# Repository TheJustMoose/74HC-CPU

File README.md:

# 74HCPU

Not a very scary instruction set discrete logic processor.

* 8 bit data
* 16 bit address / 64KB RAM
* 16 instructions
* 8 data registers and 4 pointer registers in 2 banks
* 1 flag register in IO port

## How CPU works?

[Layers of PCBs](layers/README.md)

## Instruction list

```
|----------------------------------------------|f|
|   HIGH BYTE    |    LOW BYTE   |  HIGH BYTE  |a|
|0 1 2 3  4 5 6 7 8 9 A B C D E F|   (again)   |g|
|   4   +   3 + 1 + 3  +    5    = 16          |l|
|----------------------------------------------|s|
|   ADD |  DST |C| SRC |-|Z|z|I|i| 00 0000 0000|*|
|  ADDC |  DST |C| SRC |F|Z|z|I|i| 10 0001 0000|*|
|   AND |  DST |C| SRC |-|Z|z|I|i| 20 0010 0000|*|
|    OR |  DST |C| SRC |-|Z|z|I|i| 30 0011 0000|*|
|   XOR |  DST |C| SRC |-|Z|z|I|i| 40 0100 0000|*|
|   MUL |  DST |C| SRC |-|Z|z|I|i| 50 0101 0000|*|
|   UNO |  DST |0|-|TYP|F|-|-|-|-| 60 0110 0000|*|
|   MOV |  DST |0| SRC |*|Z|z|I|i| 70 0111 0000| |
|   LPM |  DST |W|EXT|D|U|OFFSET4| 80 1000 0000| |
|    LD |  DST |0|EXT|D|U|OFFSET4| 90 1001 0000| |
|    IN |  DST |  PORT   |Z|z|I|i| A0 1010 0000| |
|--------------|7-8-9-A-B|-------|-------------|-|
|   OUT |  SRC |  PORT   |O|o|X|x| B0 1011 0000| |
|    ST |  SRC |0|EXT|D|U|OFFSET4| C0 1100 0000| |
|   CMP |  DST |C| SRC |-|   -   | D0 1101 0000|+|
|  CMPC |  DST |C| SRC |-|   -   | E0 1110 0000|+|
| BRNCH |  CALL  | 8 bit OFFSET  | F0 1111 0000| |
| BRNCH |   JMP  | 8 bit OFFSET  | F1 1111 0001| |
| BRNCH |   RET  | 8 bit +STACK  | F2 1111 0010| |
| BRNCH |  RETI  | 8 bit OFFSET  | F3 1111 0011| |
| BRNCH |    JL  | 8 bit OFFSET  | F4 1111 0100| |
| BRNCH |    JE  | 8 bit OFFSET  | F5 1111 0101| |
| BRNCH |   JNE  | 8 bit OFFSET  | F6 1111 0110| |
| BRNCH |    JG  | 8 bit OFFSET  | F7 1111 0111| |
| BRNCH |    JZ  | 8 bit OFFSET  | F8 1111 1000| |
| BRNCH |   JNZ  | 8 bit OFFSET  | F9 1111 1001| |
| BRNCH |    JC  | 8 bit OFFSET  | FA 1111 1010| |
| BRNCH |   JNC  | 8 bit OFFSET  | FB 1111 1011| |
| BRNCH |   JHC  | 8 bit OFFSET  | FC 1111 1100| |
| BRNCH |  JNHC  | 8 bit OFFSET  | FD 1111 1101| |
| BRNCH | AFCALL | Hi 8 bit ADDR | FE 1111 1110| |
| BRNCH |NOP/STOP|   1111 111x   | FF 1111 1111| |
|----------------------------------------------|-|
```

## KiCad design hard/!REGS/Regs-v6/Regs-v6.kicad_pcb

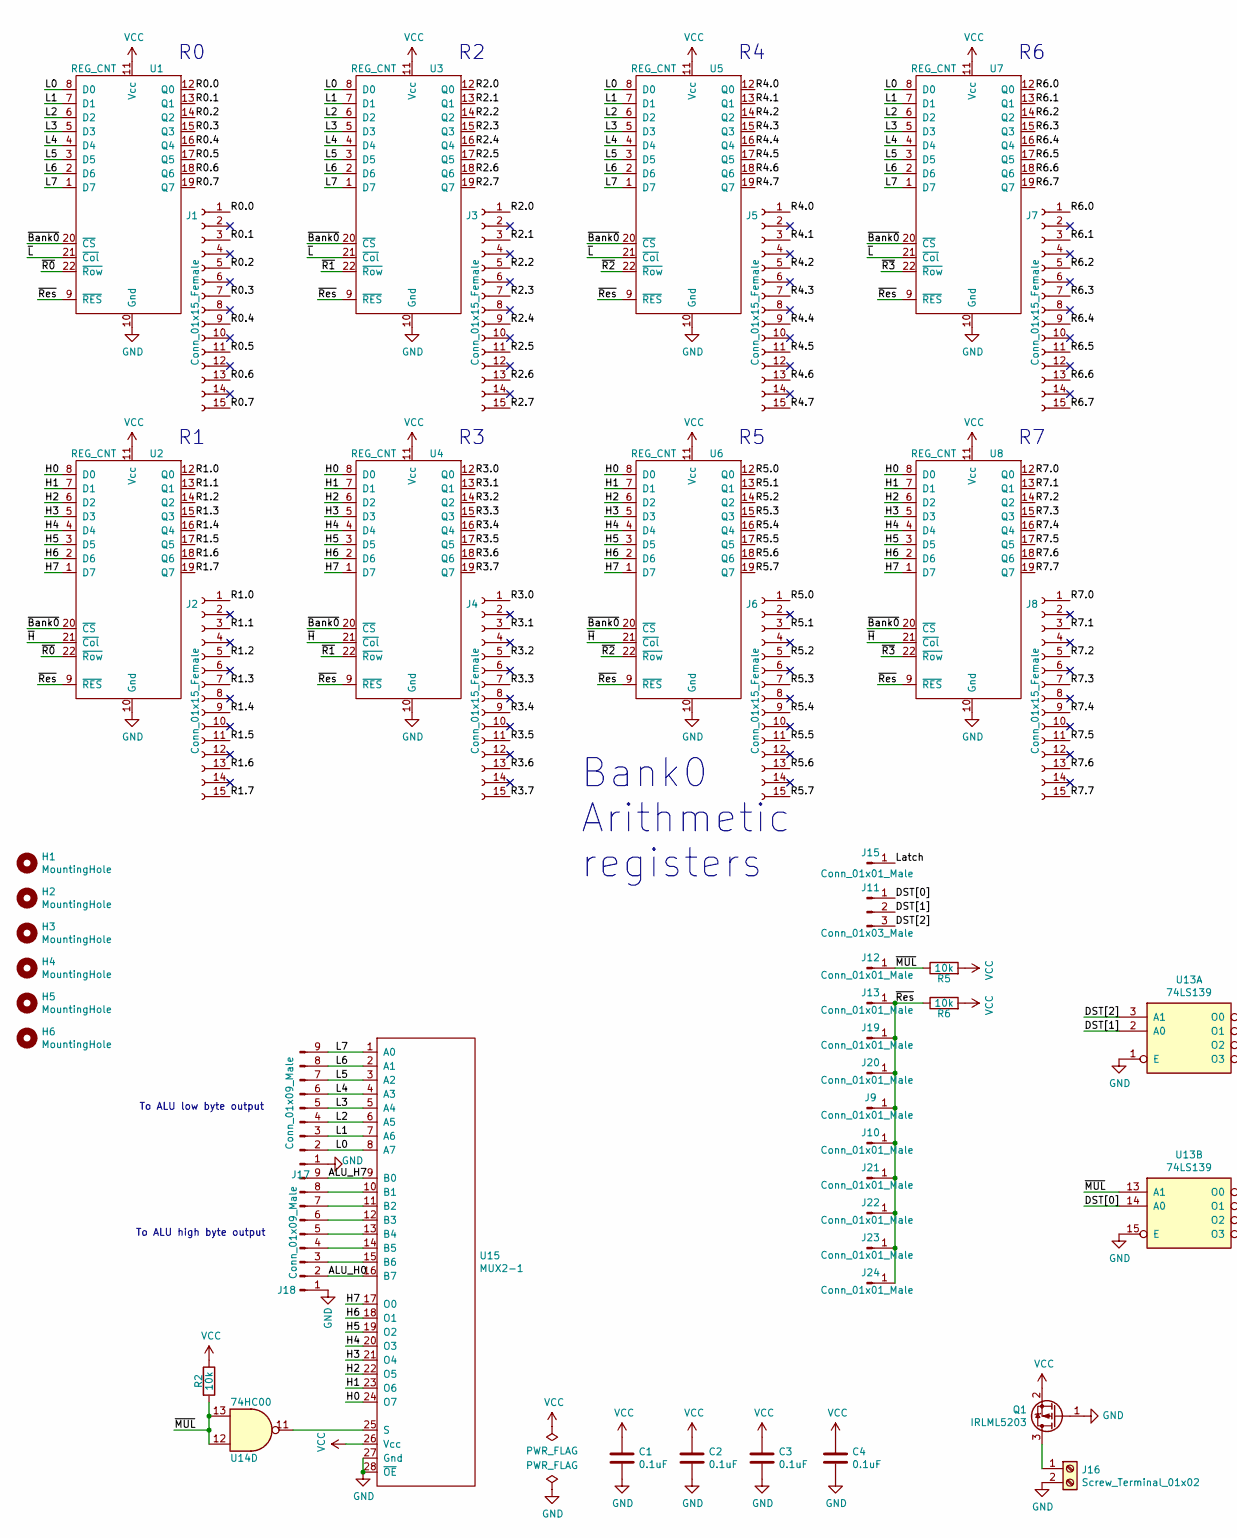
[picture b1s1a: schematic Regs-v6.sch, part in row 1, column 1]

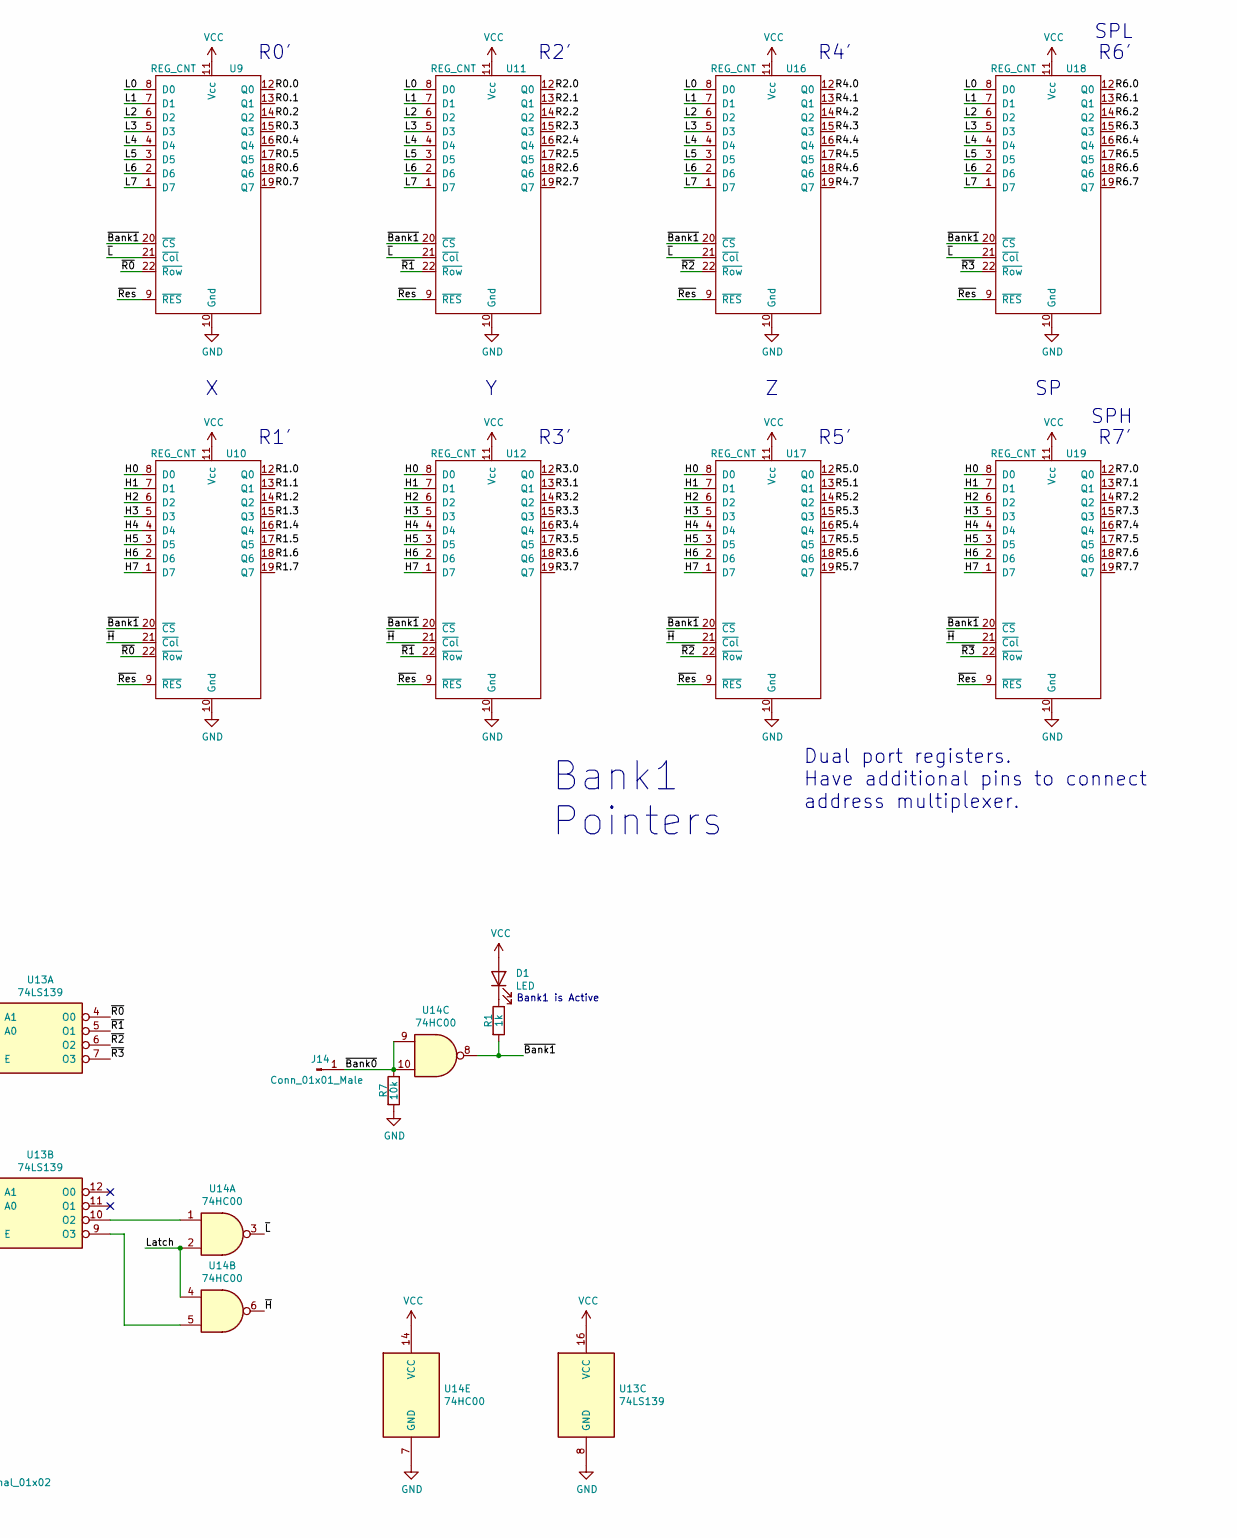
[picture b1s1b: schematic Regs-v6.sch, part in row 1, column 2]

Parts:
C1, C2, C3, C4: 0.1uF; C_0805_2012Metric_Pad1.18x1.45mm_HandSolder
D1: LED; LED_D5.0mm
H1, H2, H3, H4, H5, H6: MountingHole; MountingHole_3.2mm_M3
J1, J2, J3, J4, J5, J6, J7, J8: Conn_01x15_Female; PinSocket_1x15_P2.54mm_Vertical
J9, J10, J12, J13, J14, J15, J19, J20, J21, J22, J23, J24: Conn_01x01_Male; PinHeader_1x01_P2.54mm_Vertical
J11: Conn_01x03_Male; PinHeader_1x03_P2.54mm_Vertical
J16: Screw_Terminal_01x02; TerminalBlock_Phoenix_MKDS-1,5-2_1x02_P5.00mm_Horizontal
J17, J18: Conn_01x09_Male; PinHeader_1x09_P2.54mm_Vertical
Q1: IRLML5203; SOT-23
R1: 1k; R_0805_2012Metric_Pad1.20x1.40mm_HandSolder
R2, R5, R6, R7: 10k; R_0805_2012Metric_Pad1.20x1.40mm_HandSolder
U1, U2, U3, U4, U5, U6, U7, U8, U9, U10, U11, U12, U16, U17, U18, U19: REG_CNT
U13: 74LS139; DIP-16_W7.62mm_Socket
U14: 74HC00; DIP-14_W7.62mm_Socket
U15: MUX2-1; CMDwoC

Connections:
/ALU_H0: J18.2, U15.16 (B7)
/ALU_H7: J18.9, U15.9 (B0)
/DST[0]: J11.1, U13.14 (A0)
/DST[1]: J11.2, U13.2 (A0)
/DST[2]: J11.3, U13.3 (A1)
/H0: U2.8 (D0), U4.8 (D0), U6.8 (D0), U8.8 (D0), U10.8 (D0), U12.8 (D0), U15.24 (O7), U17.8 (D0), U19.8 (D0)
/H1: U2.7 (D1), U4.7 (D1), U6.7 (D1), U8.7 (D1), U10.7 (D1), U12.7 (D1), U15.23 (O6), U17.7 (D1), U19.7 (D1)
/H2: U2.6 (D2), U4.6 (D2), U6.6 (D2), U8.6 (D2), U10.6 (D2), U12.6 (D2), U15.22 (O5), U17.6 (D2), U19.6 (D2)
/H3: U2.5 (D3), U4.5 (D3), U6.5 (D3), U8.5 (D3), U10.5 (D3), U12.5 (D3), U15.21 (O4), U17.5 (D3), U19.5 (D3)
/H4: U2.4 (D4), U4.4 (D4), U6.4 (D4), U8.4 (D4), U10.4 (D4), U12.4 (D4), U15.20 (O3), U17.4 (D4), U19.4 (D4)
/H5: U2.3 (D5), U4.3 (D5), U6.3 (D5), U8.3 (D5), U10.3 (D5), U12.3 (D5), U15.19 (O2), U17.3 (D5), U19.3 (D5)
/H6: U2.2 (D6), U4.2 (D6), U6.2 (D6), U8.2 (D6), U10.2 (D6), U12.2 (D6), U15.18 (O1), U17.2 (D6), U19.2 (D6)
/H7: U2.1 (D7), U4.1 (D7), U6.1 (D7), U8.1 (D7), U10.1 (D7), U12.1 (D7), U15.17 (O0), U17.1 (D7), U19.1 (D7)
/L0: J17.2, U1.8 (D0), U3.8 (D0), U5.8 (D0), U7.8 (D0), U9.8 (D0), U11.8 (D0), U15.8 (A7), U16.8 (D0), U18.8 (D0)
/L1: J17.3, U1.7 (D1), U3.7 (D1), U5.7 (D1), U7.7 (D1), U9.7 (D1), U11.7 (D1), U15.7 (A6), U16.7 (D1), U18.7 (D1)
/L2: J17.4, U1.6 (D2), U3.6 (D2), U5.6 (D2), U7.6 (D2), U9.6 (D2), U11.6 (D2), U15.6 (A5), U16.6 (D2), U18.6 (D2)
/L3: J17.5, U1.5 (D3), U3.5 (D3), U5.5 (D3), U7.5 (D3), U9.5 (D3), U11.5 (D3), U15.5 (A4), U16.5 (D3), U18.5 (D3)
/L4: J17.6, U1.4 (D4), U3.4 (D4), U5.4 (D4), U7.4 (D4), U9.4 (D4), U11.4 (D4), U15.4 (A3), U16.4 (D4), U18.4 (D4)
/L5: J17.7, U1.3 (D5), U3.3 (D5), U5.3 (D5), U7.3 (D5), U9.3 (D5), U11.3 (D5), U15.3 (A2), U16.3 (D5), U18.3 (D5)
/L6: J17.8, U1.2 (D6), U3.2 (D6), U5.2 (D6), U7.2 (D6), U9.2 (D6), U11.2 (D6), U15.2 (A1), U16.2 (D6), U18.2 (D6)
/L7: J17.9, U1.1 (D7), U3.1 (D7), U5.1 (D7), U7.1 (D7), U9.1 (D7), U11.1 (D7), U15.1 (A0), U16.1 (D7), U18.1 (D7)
/Latch: J15.1, U14.2, U14.4
/R0.0: J1.1, U1.12 (Q0), U9.12 (Q0)
/R0.1: J1.3, U1.13 (Q1), U9.13 (Q1)
/R0.2: J1.5, U1.14 (Q2), U9.14 (Q2)
/R0.3: J1.7, U1.15 (Q3), U9.15 (Q3)
/R0.4: J1.9, U1.16 (Q4), U9.16 (Q4)
/R0.5: J1.11, U1.17 (Q5), U9.17 (Q5)
/R0.6: J1.13, U1.18 (Q6), U9.18 (Q6)
/R0.7: J1.15, U1.19 (Q7), U9.19 (Q7)
/R1.0: J2.1, U2.12 (Q0), U10.12 (Q0)
/R1.1: J2.3, U2.13 (Q1), U10.13 (Q1)
/R1.2: J2.5, U2.14 (Q2), U10.14 (Q2)
/R1.3: J2.7, U2.15 (Q3), U10.15 (Q3)
/R1.4: J2.9, U2.16 (Q4), U10.16 (Q4)
/R1.5: J2.11, U2.17 (Q5), U10.17 (Q5)
/R1.6: J2.13, U2.18 (Q6), U10.18 (Q6)
/R1.7: J2.15, U2.19 (Q7), U10.19 (Q7)
/R2.0: J3.1, U3.12 (Q0), U11.12 (Q0)
/R2.1: J3.3, U3.13 (Q1), U11.13 (Q1)
/R2.2: J3.5, U3.14 (Q2), U11.14 (Q2)
/R2.3: J3.7, U3.15 (Q3), U11.15 (Q3)
/R2.4: J3.9, U3.16 (Q4), U11.16 (Q4)
/R2.5: J3.11, U3.17 (Q5), U11.17 (Q5)
/R2.6: J3.13, U3.18 (Q6), U11.18 (Q6)
/R2.7: J3.15, U3.19 (Q7), U11.19 (Q7)
/R3.0: J4.1, U4.12 (Q0), U12.12 (Q0)
/R3.1: J4.3, U4.13 (Q1), U12.13 (Q1)
/R3.2: J4.5, U4.14 (Q2), U12.14 (Q2)
/R3.3: J4.7, U4.15 (Q3), U12.15 (Q3)
/R3.4: J4.9, U4.16 (Q4), U12.16 (Q4)
/R3.5: J4.11, U4.17 (Q5), U12.17 (Q5)
/R3.6: J4.13, U4.18 (Q6), U12.18 (Q6)
/R3.7: J4.15, U4.19 (Q7), U12.19 (Q7)
/R4.0: J5.1, U5.12 (Q0), U16.12 (Q0)
/R4.1: J5.3, U5.13 (Q1), U16.13 (Q1)
/R4.2: J5.5, U5.14 (Q2), U16.14 (Q2)
/R4.3: J5.7, U5.15 (Q3), U16.15 (Q3)
/R4.4: J5.9, U5.16 (Q4), U16.16 (Q4)
/R4.5: J5.11, U5.17 (Q5), U16.17 (Q5)
/R4.6: J5.13, U5.18 (Q6), U16.18 (Q6)
/R4.7: J5.15, U5.19 (Q7), U16.19 (Q7)
/R5.0: J6.1, U6.12 (Q0), U17.12 (Q0)
/R5.1: J6.3, U6.13 (Q1), U17.13 (Q1)
/R5.2: J6.5, U6.14 (Q2), U17.14 (Q2)
/R5.3: J6.7, U6.15 (Q3), U17.15 (Q3)
/R5.4: J6.9, U6.16 (Q4), U17.16 (Q4)
/R5.5: J6.11, U6.17 (Q5), U17.17 (Q5)
/R5.6: J6.13, U6.18 (Q6), U17.18 (Q6)
/R5.7: J6.15, U6.19 (Q7), U17.19 (Q7)
/R6.0: J7.1, U7.12 (Q0), U18.12 (Q0)
/R6.1: J7.3, U7.13 (Q1), U18.13 (Q1)
/R6.2: J7.5, U7.14 (Q2), U18.14 (Q2)
/R6.3: J7.7, U7.15 (Q3), U18.15 (Q3)
/R6.4: J7.9, U7.16 (Q4), U18.16 (Q4)
/R6.5: J7.11, U7.17 (Q5), U18.17 (Q5)
/R6.6: J7.13, U7.18 (Q6), U18.18 (Q6)
/R6.7: J7.15, U7.19 (Q7), U18.19 (Q7)
/R7.0: J8.1, U8.12 (Q0), U19.12 (Q0)
/R7.1: J8.3, U8.13 (Q1), U19.13 (Q1)
/R7.2: J8.5, U8.14 (Q2), U19.14 (Q2)
/R7.3: J8.7, U8.15 (Q3), U19.15 (Q3)
/R7.4: J8.9, U8.16 (Q4), U19.16 (Q4)
/R7.5: J8.11, U8.17 (Q5), U19.17 (Q5)
/R7.6: J8.13, U8.18 (Q6), U19.18 (Q6)
/R7.7: J8.15, U8.19 (Q7), U19.19 (Q7)
/~Bank0: J14.1, R7.1, U1.20 (~CS), U2.20 (~CS), U3.20 (~CS), U4.20 (~CS), U5.20 (~CS), U6.20 (~CS), U7.20 (~CS), U8.20 (~CS), U14.9, U14.10
/~Bank1: R1.2, U9.20 (~CS), U10.20 (~CS), U11.20 (~CS), U12.20 (~CS), U14.8, U16.20 (~CS), U17.20 (~CS), U18.20 (~CS), U19.20 (~CS)
/~H: U2.21 (~Col), U4.21 (~Col), U6.21 (~Col), U8.21 (~Col), U10.21 (~Col), U12.21 (~Col), U14.6, U17.21 (~Col), U19.21 (~Col)
/~L: U1.21 (~Col), U3.21 (~Col), U5.21 (~Col), U7.21 (~Col), U9.21 (~Col), U11.21 (~Col), U14.3, U16.21 (~Col), U18.21 (~Col)
/~MUL: J12.1, R2.2, R5.1, U13.13 (A1), U14.12, U14.13
/~R0: U1.22 (~Row), U2.22 (~Row), U9.22 (~Row), U10.22 (~Row), U13.4 (O0)
/~R1: U3.22 (~Row), U4.22 (~Row), U11.22 (~Row), U12.22 (~Row), U13.5 (O1)
/~R2: U5.22 (~Row), U6.22 (~Row), U13.6 (O2), U16.22 (~Row), U17.22 (~Row)
/~R3: U7.22 (~Row), U8.22 (~Row), U13.7 (O3), U18.22 (~Row), U19.22 (~Row)
/~Res: J9.1, J10.1, J13.1, J19.1, J20.1, J21.1, J22.1, J23.1, J24.1, R6.1, U1.9 (~RES), U2.9 (~RES), U3.9 (~RES), U4.9 (~RES), U5.9 (~RES), U6.9 (~RES), U7.9 (~RES), U8.9 (~RES), U9.9 (~RES), U10.9 (~RES), U11.9 (~RES), U12.9 (~RES), U16.9 (~RES), U17.9 (~RES), U18.9 (~RES), U19.9 (~RES)
GND: C1.2, C2.2, C3.2, C4.2, J16.2, J17.1, J18.1, Q1.1 (G), R7.2, U1.10 (Gnd), U2.10 (Gnd), U3.10 (Gnd), U4.10 (Gnd), U5.10 (Gnd), U6.10 (Gnd), U7.10 (Gnd), U8.10 (Gnd), U9.10 (Gnd), U10.10 (Gnd), U11.10 (Gnd), U12.10 (Gnd), U13.1 (E), U13.8 (GND), U13.15 (E), U14.7 (GND), U15.27 (Gnd), U15.28 (~OE), U16.10 (Gnd), U17.10 (Gnd), U18.10 (Gnd), U19.10 (Gnd)
unnamed: D1.1 (K), R1.1
unnamed: J16.1, Q1.3 (D)
unnamed: J18.3, U15.15 (B6)
unnamed: J18.4, U15.14 (B5)
unnamed: J18.5, U15.13 (B4)
unnamed: J18.6, U15.12 (B3)
unnamed: J18.7, U15.11 (B2)
unnamed: J18.8, U15.10 (B1)
unnamed: U13.9 (O3), U14.5
unnamed: U13.10 (O2), U14.1
unnamed: U14.11, U15.25 (S)
VCC: C1.1, C2.1, C3.1, C4.1, D1.2 (A), Q1.2 (S), R2.1, R5.2, R6.2, U1.11 (Vcc), U2.11 (Vcc), U3.11 (Vcc), U4.11 (Vcc), U5.11 (Vcc), U6.11 (Vcc), U7.11 (Vcc), U8.11 (Vcc), U9.11 (Vcc), U10.11 (Vcc), U11.11 (Vcc), U12.11 (Vcc), U13.16 (VCC), U14.14 (VCC), U15.26 (Vcc), U16.11 (Vcc), U17.11 (Vcc), U18.11 (Vcc), U19.11 (Vcc)

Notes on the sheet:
SPL
SPH
To ALU low byte output
To ALU high byte output
R0'
R4'
R2'
R6'
R7'
R5'
R3'
R1'
Bank0 Arithmetic registers
Bank1 Pointers
Dual port registers. Have additional pins to connect address multiplexer.
Bank1 is Active

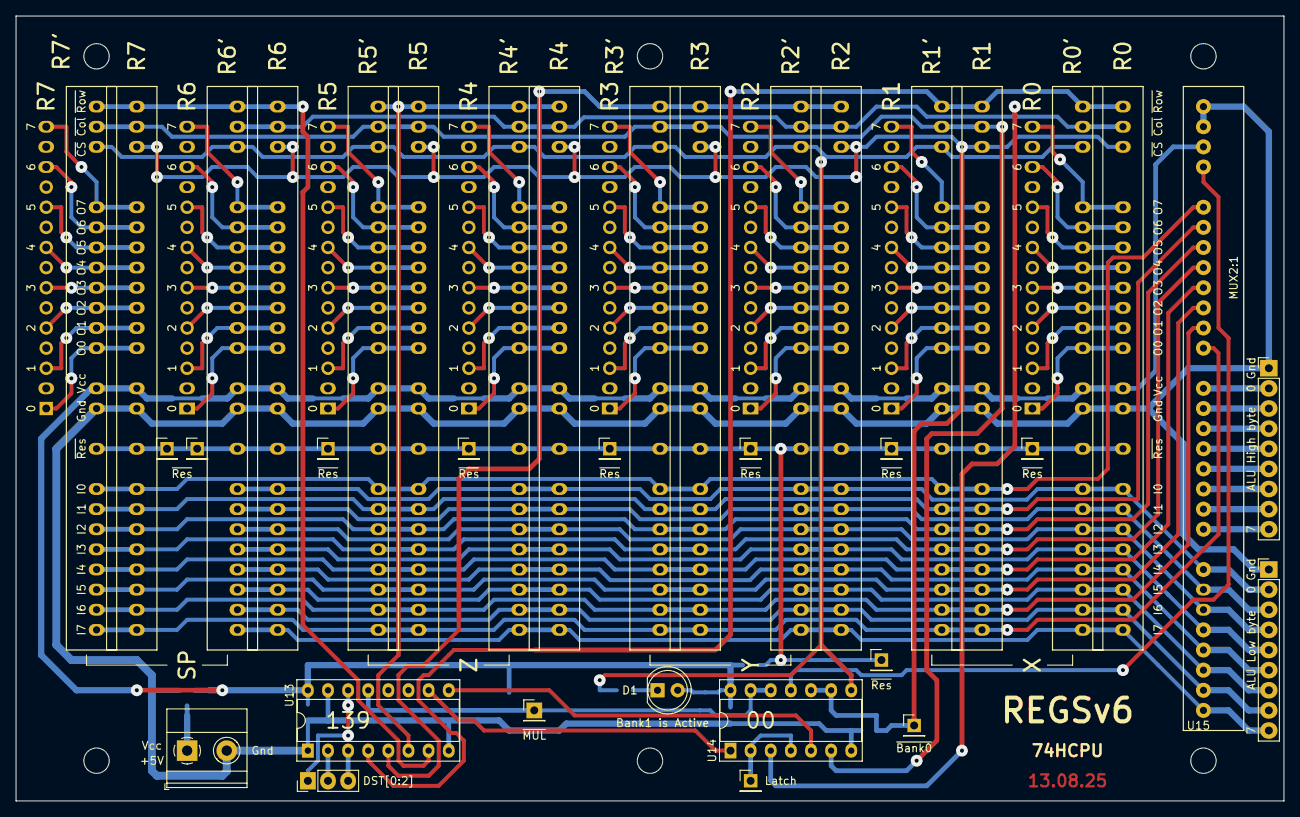
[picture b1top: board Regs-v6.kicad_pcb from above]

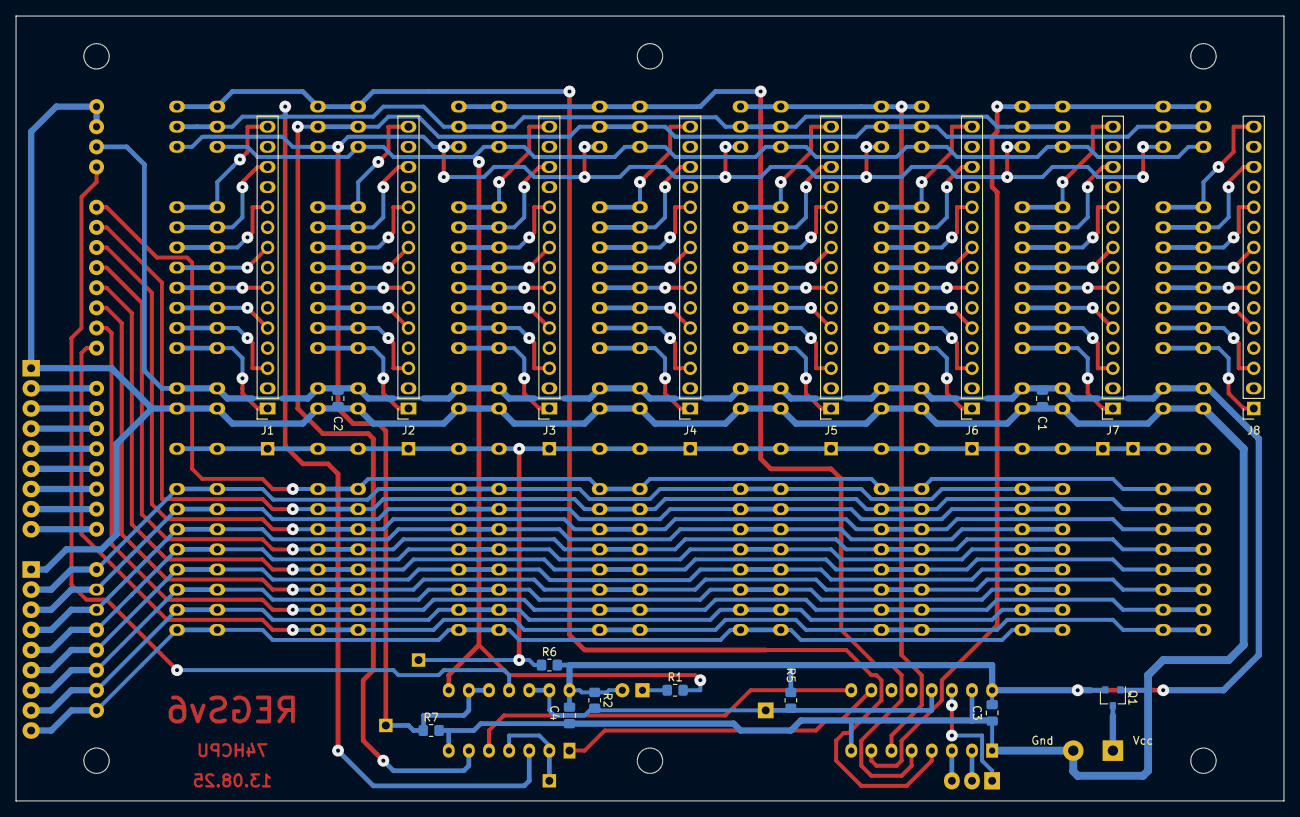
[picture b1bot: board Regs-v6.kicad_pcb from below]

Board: 2 copper layers, 160.0 x 99.1 mm, 60 parts (18 on the bottom side), 109 nets.

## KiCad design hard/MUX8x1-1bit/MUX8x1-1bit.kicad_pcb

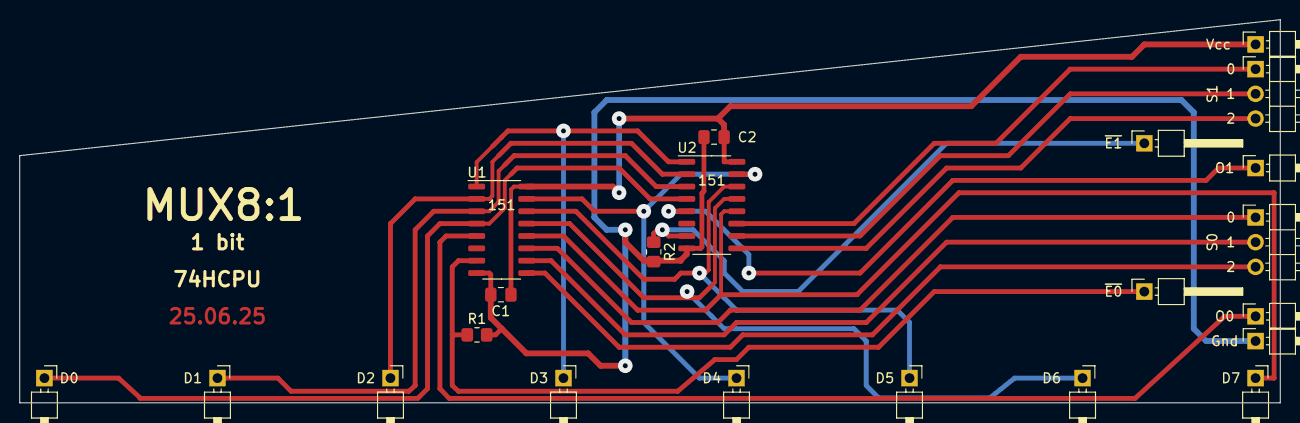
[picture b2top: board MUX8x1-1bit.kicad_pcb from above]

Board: 2 copper layers, 129.5 x 39.4 mm, 22 parts (0 on the bottom side), 20 nets.

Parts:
C1, C2: 0.1uF; C_0805_2012Metric_Pad1.18x1.45mm_HandSolder
J1, J2, J3, J4, J5, J6, J7, J8, J10, J11, J13, J14, J15, J16: Conn_01x01_Male; PinHeader_1x01_P2.54mm_Horizontal
J9, J12: Conn_01x03_Male; PinHeader_1x03_P2.54mm_Horizontal
R1, R2: 10k; R_0805_2012Metric_Pad1.20x1.40mm_HandSolder
U1, U2: 74LS151; SO-16_3.9x9.9mm_P1.27mm

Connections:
/D0: J1.1, U1.4, U2.4
/D1: J2.1, U1.3, U2.3
/D2: J3.1, U1.2, U2.2
/D3: J4.1, U1.1, U2.1
/D4: J5.1, U1.15, U2.15
/D5: J6.1, U1.14, U2.14
/D6: J7.1, U1.13, U2.13
/D7: J8.1, U1.12, U2.12
/O0: J11.1, U1.5
/O1: J14.1, U2.5
/S0.0: J9.1, U1.11
/S0.1: J9.2, U1.10
/S0.2: J9.3, U1.9
/S1.0: J12.1, U2.11
/S1.1: J12.2, U2.10
/S1.2: J12.3, U2.9
/~E0: J10.1, R1.1, U1.7
/~E1: J13.1, R2.1, U2.7
GND: C1.2, C2.2, J16.1, R1.2, R2.2, U1.8, U2.8
VCC: C1.1, C2.1, J15.1, U1.16, U2.16

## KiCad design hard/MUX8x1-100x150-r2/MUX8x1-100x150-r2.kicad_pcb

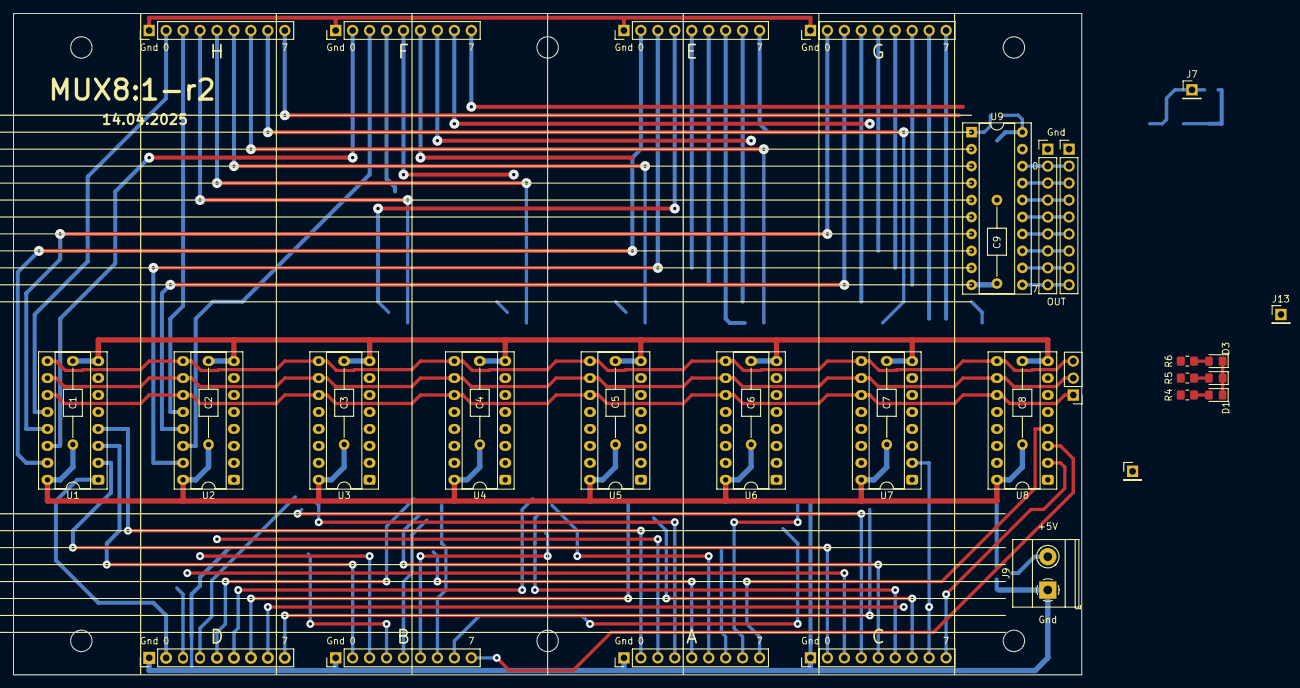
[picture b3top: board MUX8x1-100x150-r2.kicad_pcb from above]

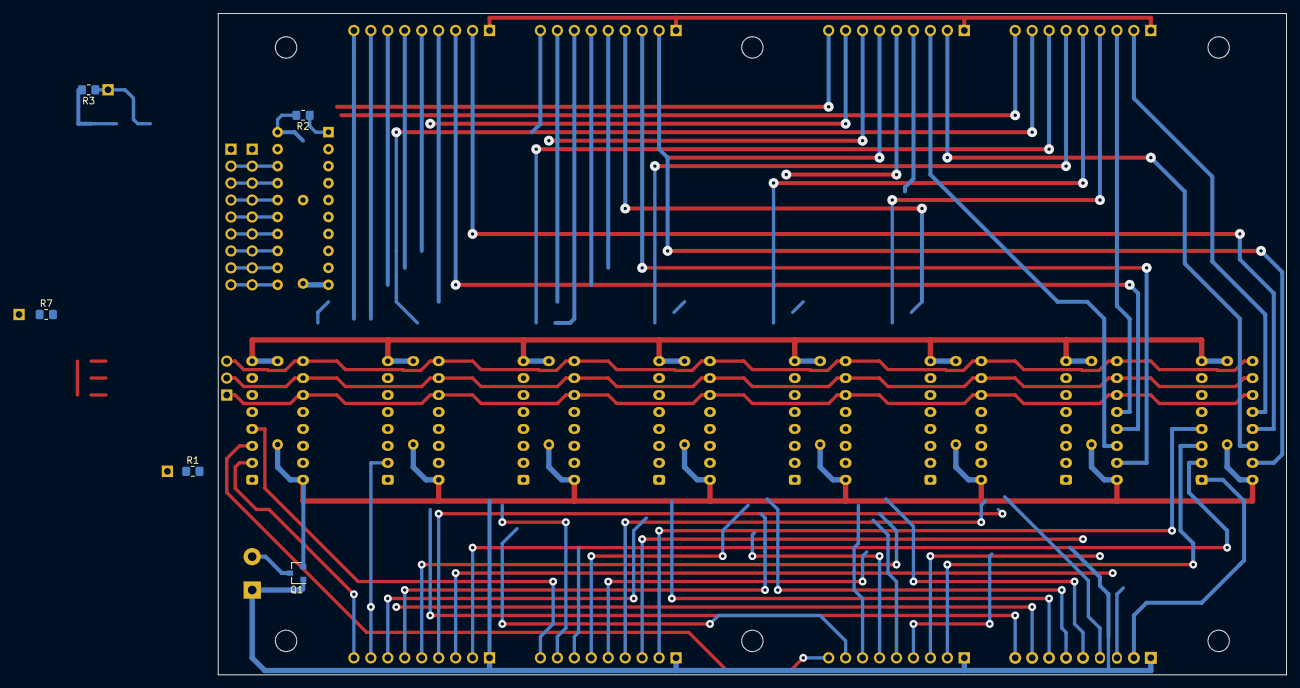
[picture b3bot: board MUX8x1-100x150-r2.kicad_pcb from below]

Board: 2 copper layers, 160.0 x 99.1 mm, 50 parts (5 on the bottom side), 93 nets.

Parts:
C1, C2, C3, C4, C5, C6, C7, C8, C9: 0.1uF; C_Axial_L3.8mm_D2.6mm_P12.50mm_Horizontal
D1, D2, D3: LED; LED_0805_2012Metric_Pad1.15x1.40mm_HandSolder
H1, H2, H3, H4, H5, H6: MountingHole; MountingHole_3.2mm_M3
J1, J2, J3, J5, J6, J11, J12, J15, J16, J21: Conn_01x09_Male; PinHeader_1x09_P2.54mm_Vertical
J7, J13, J20: Conn_01x01_Male; PinHeader_1x01_P2.54mm_Vertical
J9: Screw_Terminal_01x02; TerminalBlock_Phoenix_MKDS-1,5-2_1x02_P5.00mm_Horizontal
J10: Conn_01x03_Male; PinHeader_1x03_P2.54mm_Vertical
Q1: IRLML5203; SOT-23
R1, R2, R3, R7: 10k; R_0805_2012Metric_Pad1.20x1.40mm_HandSolder
R4, R5, R6: 1k; R_0805_2012Metric_Pad1.20x1.40mm_HandSolder
U1, U2, U3, U4, U5, U6, U7, U8: 74LS151; DIP-16_W7.62mm_Socket
U9: 74HC245; DIP-20_W7.62mm_Socket

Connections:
/A0: J1.2, U1.4
/A1: J1.3, U2.4
/A2: J1.4, U3.4
/A3: J1.5, U4.4
/A4: J1.6, U5.4
/A5: J1.7, U6.4
/A6: J1.8, U7.4
/A7: J1.9, U8.4
/B0: J5.2, U1.3
/B1: J5.3, U2.3
/B2: J5.4, U3.3
/B3: J5.5, U4.3
/B4: J5.6, U5.3
/B5: J5.7, U6.3
/B6: J5.8, U7.3
/B7: J5.9, U8.3
/BUS0: J3.2, J21.2, U9.18
/BUS1: J3.3, J21.3, U9.17
/BUS2: J3.4, J21.4, U9.16
/BUS3: J3.5, J21.5, U9.15
/BUS4: J3.6, J21.6, U9.14
/BUS5: J3.7, J21.7, U9.13
/BUS6: J3.8, J21.8, U9.12
/BUS7: J3.9, J21.9, U9.11
/C0: J11.2, U1.2
/C1: J11.3, U2.2
/C2: J11.4, U3.2
/C3: J11.5, U4.2
/C4: J11.6, U5.2
/C5: J11.7, U6.2
/C6: J11.8, U7.2
/C7: J11.9, U8.2
/D0: J15.2, U1.1
/D1: J15.3, U2.1
/D2: J15.4, U3.1
/D3: J15.5, U4.1
/D4: J15.6, U5.1
/D5: J15.7, U6.1
/D6: J15.8, U7.1
/D7: J15.9, U8.1
/E0: J2.2, U1.15
/E1: J2.3, U2.15
/E2: J2.4, U3.15
/E3: J2.5, U4.15
/E4: J2.6, U5.15
/E5: J2.7, U6.15
/E6: J2.8, U7.15
/E7: J2.9, U8.15
/F0: J6.2, U1.14
/F1: J6.3, U2.14
/F2: J6.4, U3.14
/F3: J6.5, U4.14
/F4: J6.6, U5.14
/F5: J6.7, U6.14
/F6: J6.8, U7.14
/F7: J6.9, U8.14
/G0: J12.2, U1.13
/G1: J12.3, U2.13
/G2: J12.4, U3.13
/G3: J12.5, U4.13
/G4: J12.6, U5.13
/G5: J12.7, U6.13
/G6: J12.8, U7.13
/G7: J12.9, U8.13
/H0: J16.2, U1.12
/H1: J16.3, U2.12
/H2: J16.4, U3.12
/H3: J16.5, U4.12
/H4: J16.6, U5.12
/H5: J16.7, U6.12
/H6: J16.8, U7.12
/H7: J16.9, U8.12
/O0: U1.5, U9.2
/O1: U2.5, U9.3
/O2: U3.5, U9.4
/O3: U4.5, U9.5
/O4: U5.5, U9.6
/O5: U6.5, U9.7
/O6: U7.5, U9.8
/O7: U8.5, U9.9
/S0: J10.1, R4.2, U1.11, U2.11, U3.11, U4.11, U5.11, U6.11, U7.11, U8.11
/S1: J10.2, R5.2, U1.10, U2.10, U3.10, U4.10, U5.10, U6.10, U7.10, U8.10
/S2: J10.3, R6.2, U1.9, U2.9, U3.9, U4.9, U5.9, U6.9, U7.9, U8.9
/~EH: J20.1, R1.1, U5.7, U6.7, U7.7, U8.7
/~EL: J13.1, R7.1, U1.7, U2.7, U3.7, U4.7
/~OE: J7.1, R3.1, U9.19
GND: C1.2, C2.2, C3.2, C4.2, C5.2, C6.2, C7.2, C8.2, C9.2, D1.1, D2.1, D3.1, J1.1, J2.1, J3.1, J5.1, J6.1, J9.1, J11.1, J12.1, J15.1, J16.1, J21.1, Q1.1, R1.2, R3.2, R7.2, U1.8, U2.8, U3.8, U4.8, U5.8, U6.8, U7.8, U8.8, U9.10
unnamed: D1.2, R4.1
unnamed: D2.2, R5.1
unnamed: D3.2, R6.1
unnamed: J9.2, Q1.3
unnamed: R2.1, U9.1
VCC: C1.1, C2.1, C3.1, C4.1, C5.1, C6.1, C7.1, C8.1, C9.1, Q1.2, R2.2, U1.16, U2.16, U3.16, U4.16, U5.16, U6.16, U7.16, U8.16, U9.20

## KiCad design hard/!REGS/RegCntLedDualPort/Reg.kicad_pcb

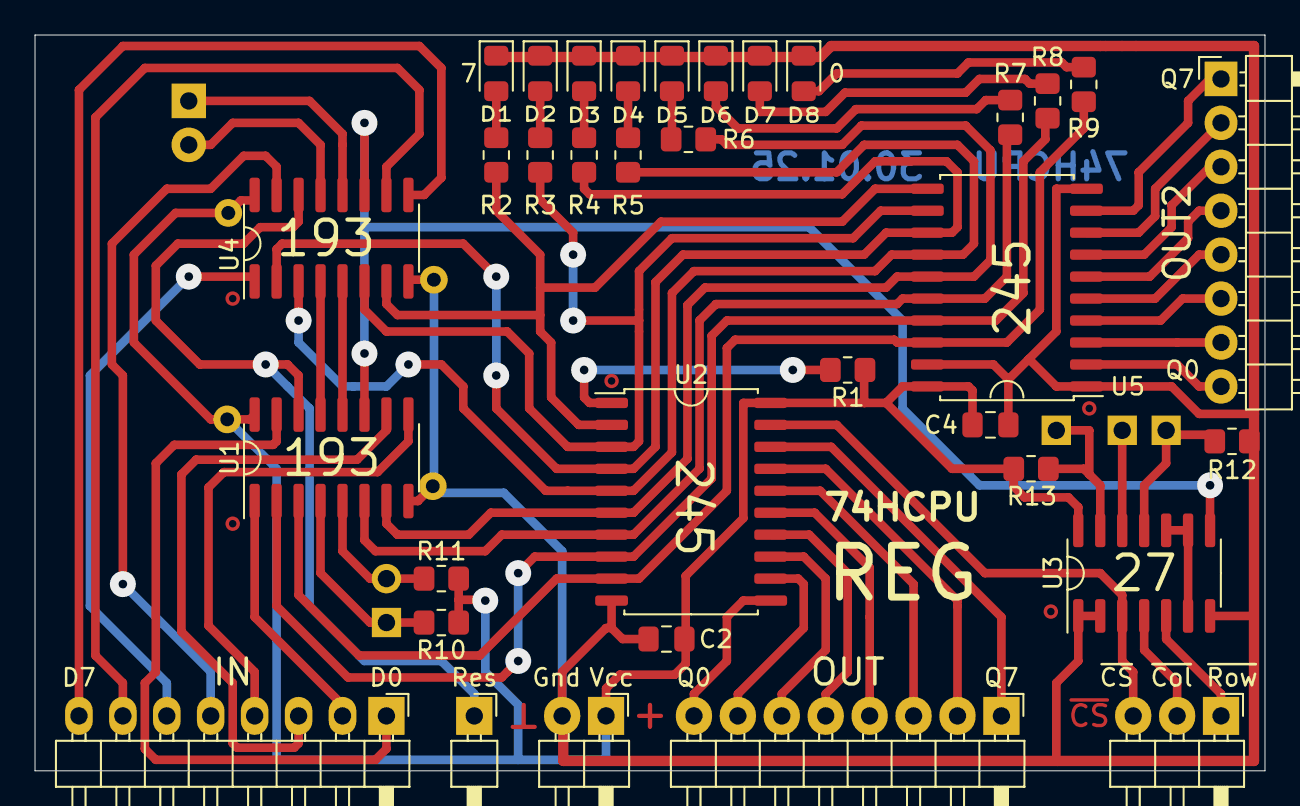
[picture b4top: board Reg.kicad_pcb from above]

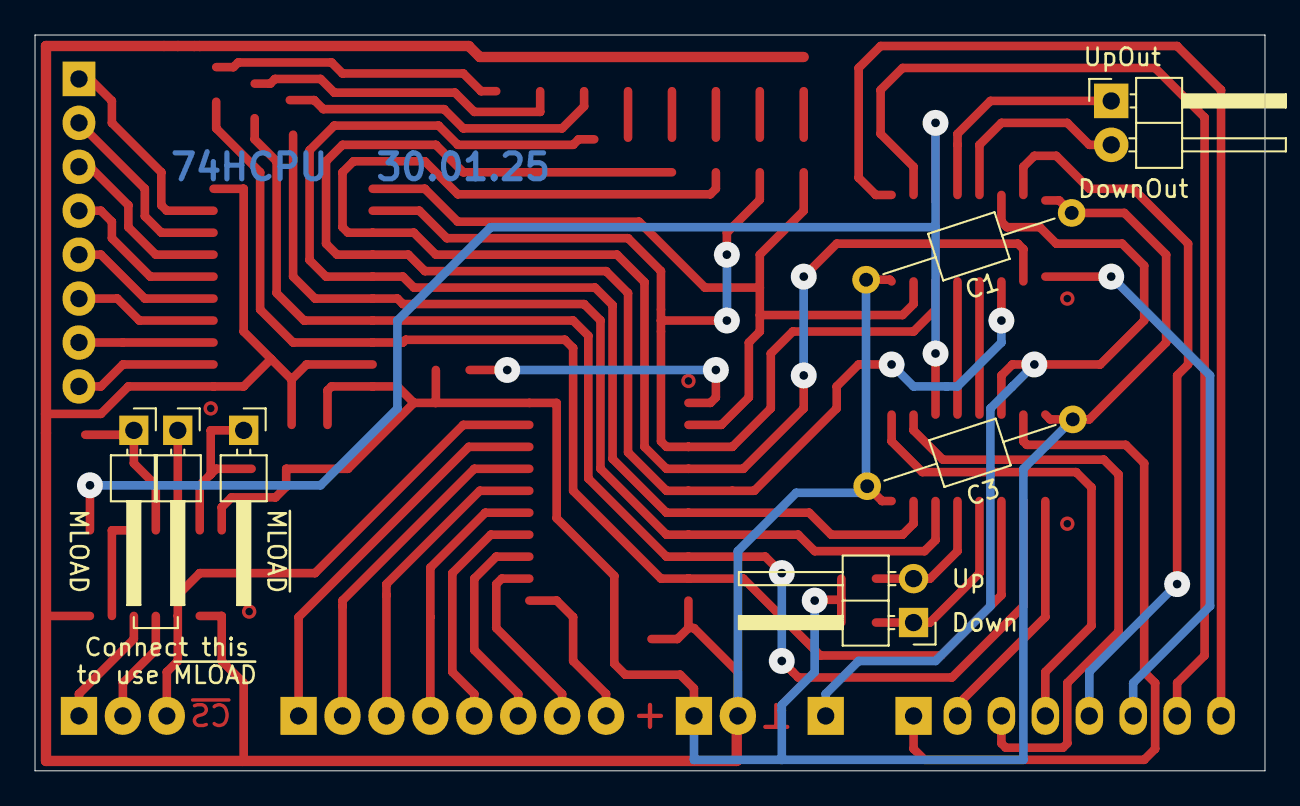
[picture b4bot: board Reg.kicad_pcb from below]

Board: 2 copper layers, 71.1 x 42.5 mm, 41 parts (7 on the bottom side), 58 nets.

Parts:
C1, C3: 0.1uF; C_Axial_L3.8mm_D2.6mm_P12.50mm_Horizontal
C2, C4: 0.1uF; C_0805_2012Metric_Pad1.18x1.45mm_HandSolder
D1, D2, D3, D4, D5, D6, D7, D8: LED; LED_0805_2012Metric_Pad1.15x1.40mm_HandSolder
J1, J2, J11: Conn_01x08_Male; PinHeader_1x08_P2.54mm_Horizontal
J3, J5, J6: Conn_01x02_Male; PinHeader_1x02_P2.54mm_Horizontal
J4: Conn_01x03_Male; PinHeader_1x03_P2.54mm_Horizontal
J7, J8, J9, J10: Conn_01x01_Male; PinHeader_1x01_P2.54mm_Horizontal
R1, R10, R11, R12, R13: 10k; R_0805_2012Metric_Pad1.20x1.40mm_HandSolder
R2, R3, R4, R5, R6, R7, R8, R9: 1k; R_0805_2012Metric_Pad1.20x1.40mm_HandSolder
U1, U4: 74LS193; SOP-16_3.9x9.9mm_P1.27mm
U2, U5: 74HC245; SOP-20_7.5x12.8mm_P1.27mm
U3: 74LS27; SO-14_3.9x8.65mm_P1.27mm

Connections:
/AQ0: J11.8, U5.2
/AQ1: J11.7, U5.3
/AQ2: J11.6, U5.4
/AQ3: J11.5, U5.5
/AQ4: J11.4, U5.6
/AQ5: J11.3, U5.7
/AQ6: J11.2, U5.8
/AQ7: J11.1, U5.9
/D0: J1.1, U1.15
/D1: J1.2, U1.1
/D2: J1.3, U1.10
/D3: J1.4, U1.9
/D4: J1.5, U4.15
/D5: J1.6, U4.1
/D6: J1.7, U4.10
/D7: J1.8, U4.9
/Down: J6.1, R10.1, U1.4
/DownLH: U1.13, U4.4
/DownOut: J5.2, U4.13
/L0: R9.1, U1.3, U2.9, U5.18
/L1: R8.1, U1.2, U2.8, U5.17
/L2: R7.1, U1.6, U2.7, U5.16
/L3: R6.1, U1.7, U2.6, U5.15
/L4: R5.1, U2.5, U4.3, U5.14
/L5: R4.1, U2.4, U4.2, U5.13
/L6: R3.1, U2.3, U4.6, U5.12
/L7: R2.1, U2.2, U4.7, U5.11
/MLOAD: J8.1, R12.2, U3.11
/Q0: J2.8, U2.11
/Q1: J2.7, U2.12
/Q2: J2.6, U2.13
/Q3: J2.5, U2.14
/Q4: J2.4, U2.15
/Q5: J2.3, U2.16
/Q6: J2.2, U2.17
/Q7: J2.1, U2.18
/Res: J7.1, U1.14, U4.14
/Up: J6.2, R11.1, U1.5
/UpLH: U1.12, U4.5
/UpOut: J5.1, U4.12
/~CS: J4.3, U2.19, U3.3
/~Col: J4.2, U3.4
/~LOAD: U1.11, U3.8, U4.11
/~MLOAD: J9.1, R13.2, U3.13
/~Row: J4.1, U3.5
GND: C1.2, C2.2, C3.2, C4.2, D1.1, D2.1, D3.1, D4.1, D5.1, D6.1, D7.1, D8.1, J3.2, R12.1, U1.8, U2.10, U3.1, U3.2, U3.7, U4.8, U5.1, U5.10, U5.19
unnamed: D1.2, R2.2
unnamed: D2.2, R3.2
unnamed: D3.2, R4.2
unnamed: D4.2, R5.2
unnamed: D5.2, R6.2
unnamed: D6.2, R7.2
unnamed: D7.2, R8.2
unnamed: D8.2, R9.2
unnamed: J10.1, U3.12
unnamed: R1.1, U2.1
unnamed: U3.6, U3.9, U3.10
VCC: C1.1, C2.1, C3.1, C4.1, J3.1, R1.2, R10.2, R11.2, R13.1, U1.16, U2.20, U3.14, U4.16, U5.20

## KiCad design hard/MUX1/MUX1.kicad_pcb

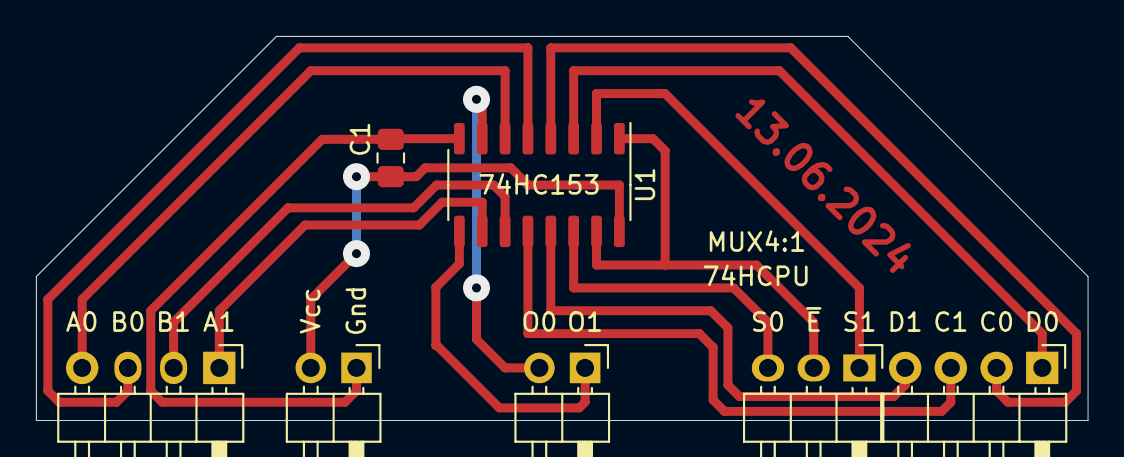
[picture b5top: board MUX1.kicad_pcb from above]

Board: 2 copper layers, 58.4 x 21.3 mm, 7 parts (0 on the bottom side), 15 nets.

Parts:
C1: 0.1uF; C_0805_2012Metric_Pad1.18x1.45mm_HandSolder
J1, J2: Conn_01x04_Male; PinHeader_1x04_P2.54mm_Horizontal
J3: Conn_01x03_Male; PinHeader_1x03_P2.54mm_Horizontal
J4, J5: Conn_01x02_Male; PinHeader_1x02_P2.54mm_Horizontal
U1: 74LS153; SO-16_3.9x9.9mm_P1.27mm

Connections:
/A0: J1.4, U1.6
/A1: J1.1, U1.10
/B0: J1.3, U1.5
/B1: J1.2, U1.11
/C0: J2.2, U1.4
/C1: J2.3, U1.12
/D0: J2.1, U1.3
/D1: J2.4, U1.13
/O0: J5.2, U1.7
/O1: J5.1, U1.9
/S0: J3.3, U1.14
/S1: J3.1, U1.2
/~E: J3.2, U1.1, U1.15
GND: C1.2, J4.1, U1.8
VCC: C1.1, J4.2, U1.16
